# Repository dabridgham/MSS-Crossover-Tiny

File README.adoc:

= MSS Crossover

A KiCad project for a circuit board that implements an
https://www.modularsignalsystem.info/index.html[MSS] Detection node
(aka Crossover node).  It includes the block detection circuit and the
crossover wiring between two RJ45 connectors.

The block detection is implemented with a resistor as the current
sense element and then an ATtiny to do the math.  The board includes
the bridge rectifier so it can be powered off the ACC bus and it uses
optoisolators to drive the MSS line.

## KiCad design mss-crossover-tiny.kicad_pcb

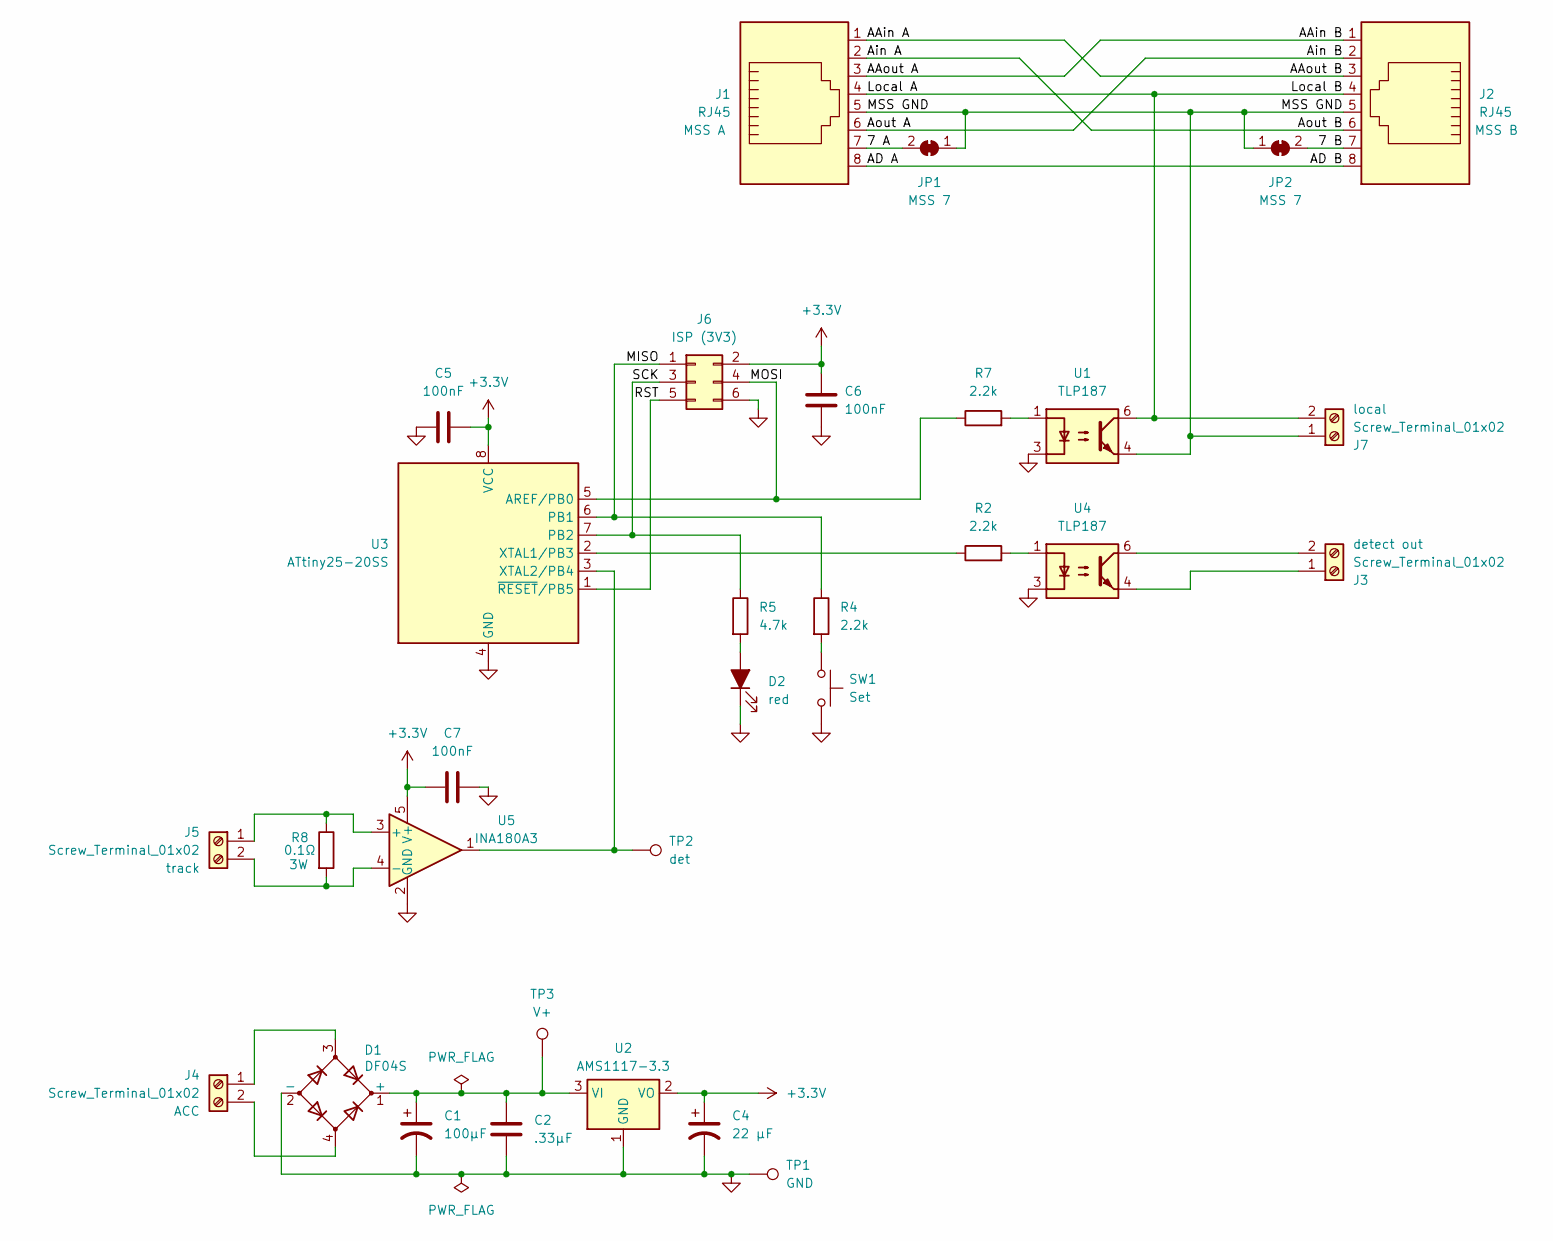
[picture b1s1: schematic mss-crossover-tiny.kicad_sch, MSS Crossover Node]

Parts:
C1: 100µF; CP_Elec_6.3x7.7; MPN EEV107M035A9HAA; JLCPCB Part C3338
C2: .33µF; C_0805_2012Metric_Pad1.18x1.45mm_HandSolder; MPN CL21B334KBFNNNE; JLCPCB Part C1737
C4: 22 µF; CP_EIA-3216-18_Kemet-A_Pad1.58x1.35mm_HandSolder; JLCPCB Part C7183
C5, C6, C7: 100nF; C_0805_2012Metric_Pad1.18x1.45mm_HandSolder; MPN CL21B104KBCNNNC
D1: DF04S; Diode_Bridge_Vishay_DFS; MPN DF04S; JLCPCB Part C5185986
D2: red; LED_0805_2012Metric_Pad1.15x1.40mm_HandSolder; MPN LTST-C170KRKT; JLCPCB Part C84256
J1, J2: RJ45; MJ3221-88; MPN MJ3221-88
J3, J4, J5, J7: Screw_Terminal_01x02; CUI_TB003-500-P02BE; MPN 691210910002
J6: ISP (3V3); Tag-Connect_TC2030-IDC-NL_2x03_P1.27mm_Vertical
JP1, JP2: MSS 7; SolderJumper-2_P1.3mm_Bridged_RoundedPad1.0x1.5mm
R2, R4, R7: 2.2k; R_0805_2012Metric_Pad1.20x1.40mm_HandSolder; MPN RC0805FR-102K2L
R5: 4.7k; R_0805_2012Metric_Pad1.20x1.40mm_HandSolder; MPN RC0805FR-104K7L
R8: 0.1Ω; R_2512_6332Metric; MPN CRA2512-FZ-R100ELF; JLCPCB Part C7419997
SW1: Set; SW_Push_1P1T_NO_CK_KMR2; MPN KMR211NG LFS; JLCPCB Part C72443
TP1: GND; TestPoint_THTPad_1.5x1.5mm_Drill0.7mm
TP2: det; TestPoint_THTPad_1.5x1.5mm_Drill0.7mm
TP3: V+; TestPoint_THTPad_1.5x1.5mm_Drill0.7mm
U1, U4: TLP187; SOIC-4_4.55x3.7mm_P2.54mm; MPN TLP187; JLCPCB Part C393886
U2: AMS1117-3.3; SOT-223-3_TabPin2; MPN AMS1117-3.3
U3: ATtiny25-20SS; SOIC-8_3.9x4.9mm_P1.27mm; MPN ATtiny25-20SSU
U5: INA180A3; SOT-23-5; MPN INA180A1IDBVR

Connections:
+3.3V: C4.1, C5.2, C6.2, C7.1, J6.2, U2.2 (VO), U3.8 (VCC), U5.5 (V+)
/7 A: J1.7, JP1.2 (B)
/7 B: J2.7, JP2.2 (B)
/AAin A: J1.1, J2.3
/AAin B: J1.3, J2.1
/AD A: J1.8, J2.8
/Ain A: J1.2, J2.6
/Ain B: J1.6, J2.2
/Local A: J1.4, J2.4, J7.2, U1.6
/MISO: J6.1, R4.1, U3.6 (PB1)
/MOSI: J6.4, R7.1, U3.5 (AREF/PB0)
/MSS GND: J1.5, J2.5, J7.1, JP1.1 (A), JP2.1 (A), U1.4
/RST: J6.5, U3.1 (~RESET/PB5)
/SCK: J6.3, R5.1, U3.7 (PB2)
GND: C1.2, C2.2, C4.2, C5.1, C6.1, C7.2, D1.2 (-), D2.1 (K), J6.6, SW1.1, TP1.1, U1.3, U2.1 (GND), U3.4 (GND), U4.3, U5.2 (GND)
unnamed: C1.1, C2.1, D1.1 (+), TP3.1, U2.3 (VI)
unnamed: D2.2 (A), R5.2
unnamed: J3.1, U4.4
unnamed: J3.2, U4.6
unnamed: D1.3, J4.1
unnamed: D1.4, J4.2
unnamed: J5.1, R8.1, U5.3 (+)
unnamed: J5.2, R8.2, U5.4 (-)
unnamed: R2.2, U4.1
unnamed: R4.2, SW1.2
unnamed: R7.2, U1.1
unnamed: R2.1, U3.2 (XTAL1/PB3)
unnamed: TP2.1, U3.3 (XTAL2/PB4), U5.1

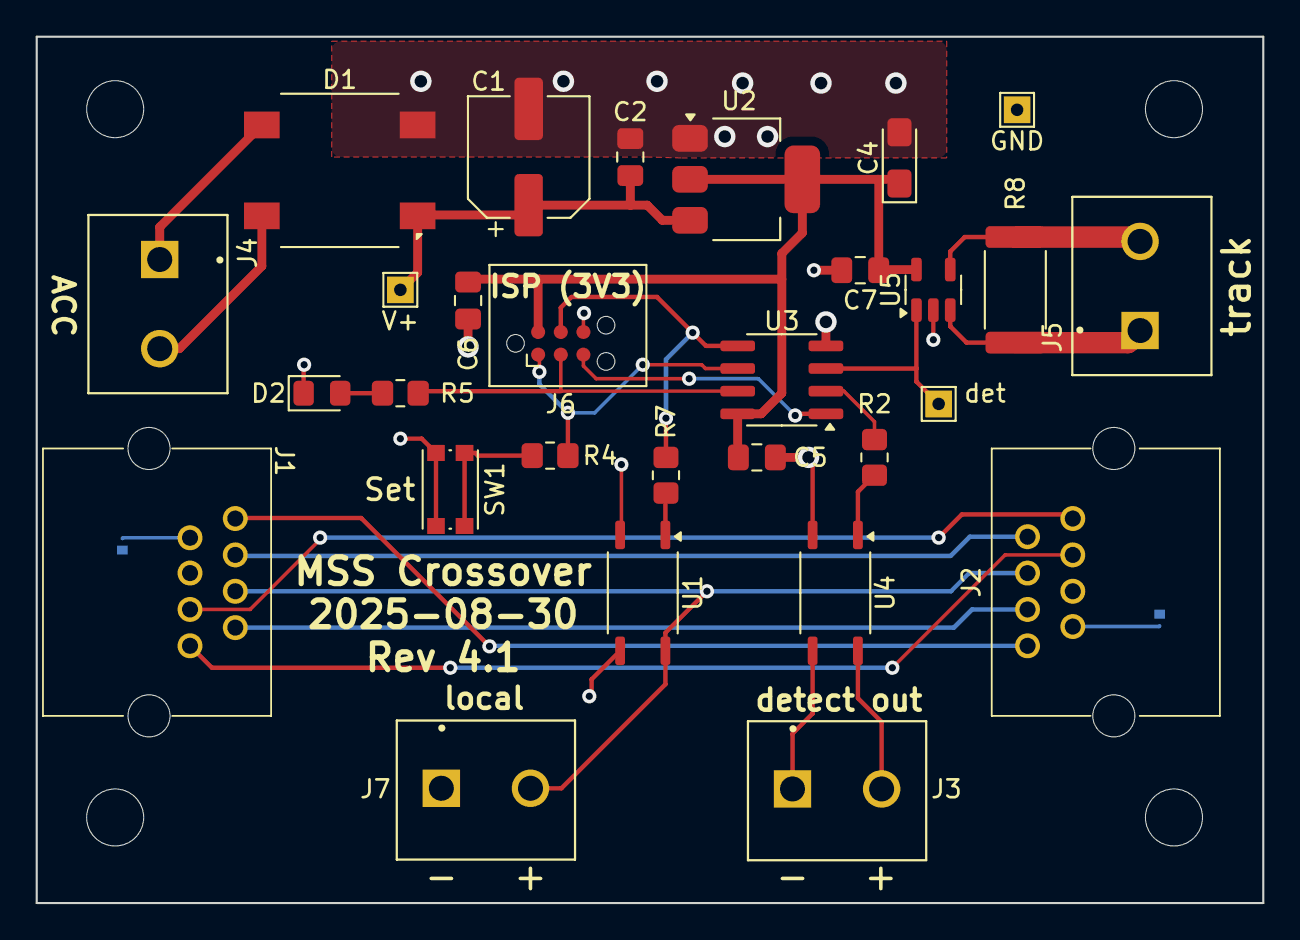
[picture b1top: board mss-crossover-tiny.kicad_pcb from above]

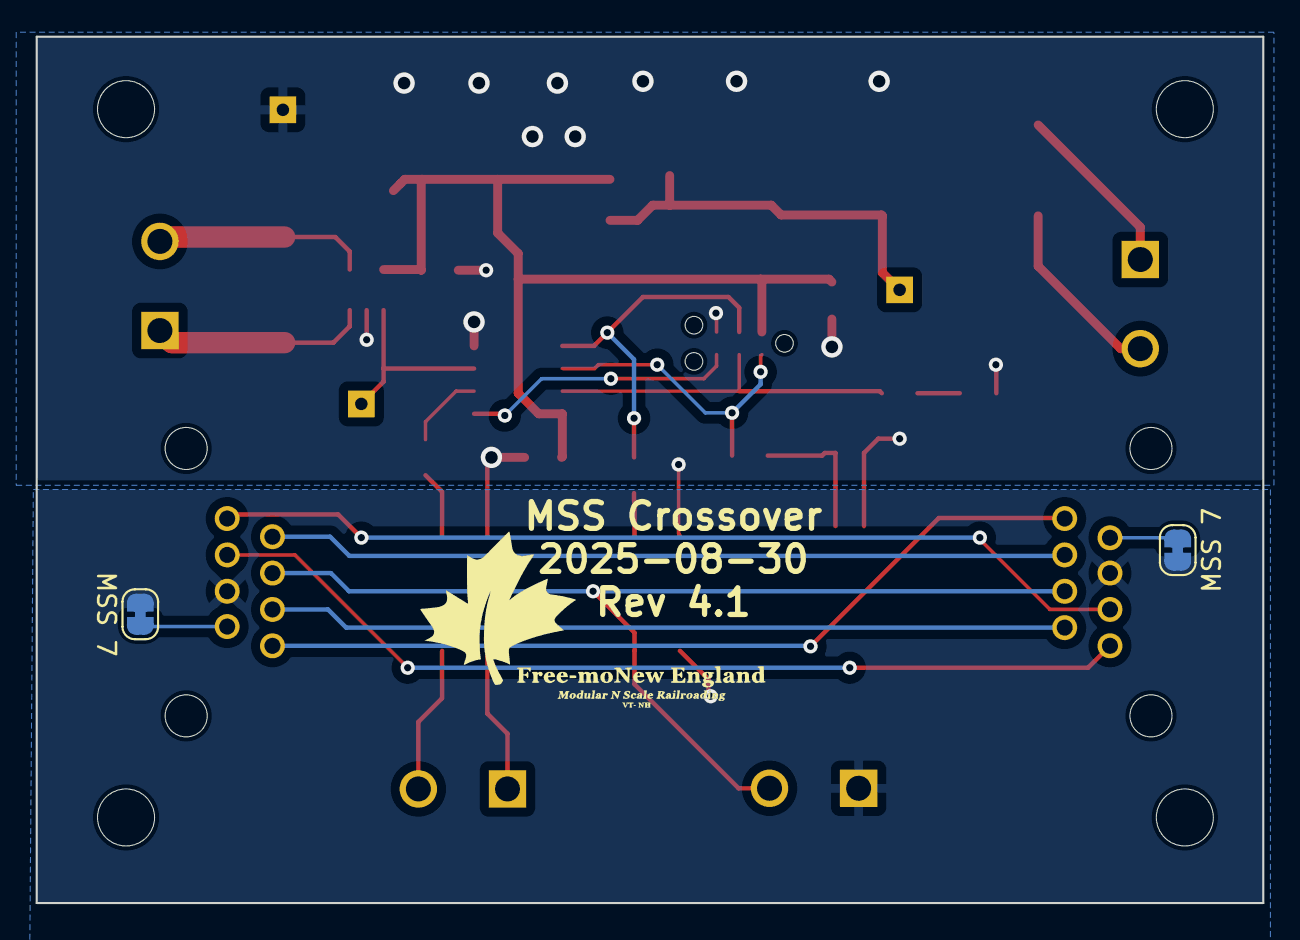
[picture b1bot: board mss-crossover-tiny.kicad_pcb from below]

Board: 2 copper layers, 68.8 x 48.6 mm, 31 parts (2 on the bottom side), 28 nets.

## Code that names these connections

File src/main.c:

#define F_CPU 1000000UL		/* default internal clock is 1 MHz (8 MHz div 8) */
#include <avr/io.h>
#include <util/delay.h>
#include <avr/io.h>
#include <avr/interrupt.h>
#include <util/atomic.h>
#include <avr/eeprom.h>

 
#define bit(n) (1<<n)
#define bit_set(reg, bit) { reg |= (1<<bit); }
#define bit_clear(reg, bit) { reg &= ~(1<<bit); }

#define LED_ON() { bit_set(PORTB, PORTB2) }
#define LED_OFF() { bit_clear(PORTB, PORTB2) }

/* Control the LED, MSS, and detect outputs */
#define OUTPUT_ON() { PORTB |= bit(PORTB3) | bit(PORTB2) | bit(PORTB0); }
#define OUTPUT_OFF() { PORTB &= ~(bit(PORTB3) | bit(PORTB2) | bit(PORTB0)); }

#define BUTTON_PUSHED() (!bit_is_set(PINB, DDB1))

const int16_t attack = 100;
const int16_t decay = 10;
const int32_t filtern = 980;	/* filter numerator */
const int32_t filterd = 1000;	/* filter denominator */
const unsigned int timeout = 2000; /* 2 seconds */
const unsigned int sample_time = 2000; /* 2 seconds */
#define filter(old, new) (((old * filtern)/filterd) + (((new * (filterd-filtern))/filterd)))

uint16_t *threshold_p = 0; /* EEPROM address for the saved threshold */

/*
 * Timer interrupt code to implement a millis() function.
 */
volatile unsigned long timer0_millis = 0;

// Initialize the timer for 1ms interrupts
void millis_init(void) {
    // Set Timer0 to CTC mode with a prescaler of 64
    TCCR0A = (1 << WGM01);
    TCCR0B = (1 << CS01) | (1 << CS00); // Prescaler 64

    // Set compare value for 1ms at 16MHz: (16,000,000 / 64) / 1000 = 250
    // Set compare value for 1ms at 1MHz: (1,000,000 / 64) / 1000 = 16
    OCR0A = 16;

    // Enable compare match interrupt
    TIMSK |= (1 << OCIE0A);

    // Enable global interrupts
    sei();
}

// Timer0 compare match interrupt service routine
ISR(TIMER0_COMPA_vect) {
    timer0_millis++;
}

// Return the number of milliseconds since the program started
unsigned long millis(void) {
    unsigned long m;
    ATOMIC_BLOCK(ATOMIC_FORCEON) {
        m = timer0_millis;
    }
    return m;
}   

/* Setup the ADC */
void adc_init()
{
  ADMUX =		  // Vref = Vcc
    bit(ADLAR) |	  // left shifted
    0x2;		  // input is single-ended PB4 (ADC2)
  DIDR0 = bit(ADC2D);	  // disable the digital inputs on ADC2
  ADCSRB = bit(BIN);	  // bipolar input mode, free running mode
  ADCSRA = bit(ADEN) |	  // enable ADC
    //    bit(ADSC) |		// start conversion
    //    bit(ADATE) |		// auto trigger enable
    bit(ADPS2) | bit(ADPS1) | bit(ADPS0); // scale ADC clock by 128

  /* setup the ADC */
  ADMUX =		  // Vref = Vcc
    bit(ADLAR) |	  // left shifted
    0x2;		  // input is single-ended PB4 (ADC2)
  DIDR0 = bit(ADC2D);	  // disable the digital inputs on ADC2
  ADCSRB = bit(BIN);	  // bipolar input mode, free running mode
  ADCSRA = bit(ADEN) |	  // enable ADC
    //    bit(ADSC) |		// start conversion
    //    bit(ADATE) |		// auto trigger enable
    bit(ADPS2) | bit(ADPS1) | bit(ADPS0); // scale ADC clock by 128
}

/* Read the A/D Converter */
uint16_t read_adc()
{
  uint8_t c_low, c_hi;

  ADCSRA |= bit(ADSC);		   /* start conversion */
  while (bit_is_set(ADCSRA, ADSC)) /* wait for ADC to finish */
    ;				   /* should probably time out */

  /* must read low then high, per the datasheet */
  c_low = ADCL;
  c_hi = ADCH;
  return (c_hi << 8) | c_low;
}

int main()
{
  int16_t amps = 0,
    hi_amps = 0,
    threshold = 1000,
    setting_threshold = 0;
  unsigned long last_hi = 0,
    current_millis = 0;

  threshold = eeprom_read_word(threshold_p); /* read the stored threshold */

  millis_init();		/* enable the millisecond counter */

  // Set pins 5 (PB0), 7 (PB2), and 2 (PB3) as outputs, all others
  // inputs
  DDRB = bit(DDB0) | bit(DDB2) | bit(DDB3); 
  PORTB |= bit(DDB1);		/* enable pullup on pin 6 (PB1) for the pushbutton */

  adc_init();			/* setup the ADC */

  while (1) {
    current_millis = millis();
    if (setting_threshold) {
      if ((current_millis - last_hi) > sample_time) {
	threshold = (hi_amps * 15) / 10; /* set threshold 50% higher */
	eeprom_write_word(threshold_p, threshold);
	setting_threshold = 0;
	last_hi = 0;
	LED_OFF();
      } else {
	/* set hi_amps to the highest reading during the sample period */
	amps = read_adc();
	if (amps > hi_amps)
	  hi_amps = amps;
      }
    } else {
      if (BUTTON_PUSHED()) {
	setting_threshold = 1;
	last_hi = current_millis; /* use last_hi for the sample timeout */
	hi_amps = 0;
	LED_ON();
      } else {
	amps = read_adc();

	/* values greater than the threshold update the time */
	if (amps > threshold)
	  last_hi = current_millis;

	/* if the last high value was more recent than timeout, set detection outputs */
	if ((current_millis - last_hi) < timeout) {
	  OUTPUT_ON();
	} else {
	  OUTPUT_OFF();
	}

	_delay_ms(1);
      }
    }
  }
}

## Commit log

2023-11-03 Initial commit. The first prototype board is built and the software is in testing. The board is exhibiting far too much noise on Vcc and the output of the current sensor.
2023-11-03 Pulled in a default .gitignore from GitHub
2023-11-04 Added test points to board. In src, added code to control the opto-isolator as well as the LED.
2023-11-04 Updated some of the MPNs
2023-11-06 Updated MPN for the ATtiny
2023-11-14 Made some macros to simplify code and moved the adc read into a subroutine.
2023-11-14 Changed to be able to plug the crossover board into a cascade board.
2023-11-25 Little updates. Moved power from 12V to ACC back to 12V.
2024-03-23 Reworked design to use a current shunt instead.
2025-02-25 Still working on then redesign for a resistive sense element. Also added optoisolators.
2025-02-25 Added in the new files created by the JLCPCB add-on
2025-02-25 Changed everything to 3.3V instead of 5V
2025-02-25 Be a bit more desriptive in the README file.
2025-03-03 Updated to KiCad v9. This is the release that was sent to JLCPCB for assembly as version 4.0.
2025-09-04 Some small changes learned from the first prototype. Switch back to the larger screw terminals and changed resistor to the pushbutton to 2.2k instead of 4.7k.
2025-09-04 Changed the code to work with the shunt current detection.
2025-09-04 Call it a Detection Node.
2025-09-04 Fixed up the threshold calculation and added reading/writing to/from the EEPROM.
